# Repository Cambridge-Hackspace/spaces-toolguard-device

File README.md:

# spaces-toolguard-device

The ToolGuard box: its firmware, and the boards it runs on (`hardware/`).

A generic tool box for [Cooperative Systems: Spaces][css], the access-control
platform at the [Cambridge Hackspace][hackspace]. One image, configured at
setup into whichever of these a machine -- or a door, or a room -- needs: a
badge reader that asks the edge and shows the answer on a 16x2 LCD; a reader
that also switches the machine; a reader that watches it work and meters the
time; a plug with no reader at all; a door box that releases a latch for the
pulse the platform names; and, on any of them, a stop button anyone may press.
A door, a tool and a room are the same resource with different bindings (CS:S
#182), and this box speaks the resource-shaped local wire.

> Work in progress. The protocol core and the display model are host-tested, and
> the firmware compiles for all four chips in CI. **Only an ESP32-C6 Super Mini
> has run it**, on the bench: the reader, the panel, a card's round trip to the
> edge, and an over-the-air update with its rollback. Its stop button, relay,
> strike and sense input have not been wired yet. The C5, C3 and S3 pin maps
> compile and nothing more, since none of those boards exists here yet.

## What it is, and is not

The box **asks**, **reports**, and — only if it is configured to switch the
machine — **energizes**, and then only on an explicit yes *and* an unexpired
lease from the edge. The protocol, the session, the lease and the metering are
`spaces_device::Module` from [`spaces-firmware`][sf]; this crate adds the
panel, the card reader, the relay, the sense input, the stop button, and the
setup page that says which of those are wired. The roles are independent and
are settings, not builds: a box registers as whatever it is configured to be,
and the platform binds it to a tool in those roles.

It is **access control and metering, not a safety device.** It must never
replace a door interlock, a guard, or an emergency stop — the stop button
included, which goes through this firmware, a lease and a Wi-Fi link.
[`docs/INSTALLING.md`](docs/INSTALLING.md) opens with why.

## Layout

| Path | What it is |
|---|---|
| `toolguard-core/` | the box as a `spaces_device::Device`: the glue over `spaces_device::Module`, the display model, and how usage is sensed. No hardware, no I/O, host-tested |
| `toolguard-fw/` | the ESP-IDF firmware: RC522 over SPI, 1602 over I2C, three chips |
| `hardware/` | the boards, as atopile and KiCad sources; licensed separately (see below) |

The protocol is not redefined here. `Module`, the topics and the wire types come
from [`spaces-firmware`][sf]'s `spaces-device`, pinned by tag in `Cargo.toml`
(currently `v0.10.0`), so this box and every other module speak the same wire by
construction.

**The local wire is signed.** A box that registration gave a command key seals
every card, stop and usage report with it, and acts on no lease or answer its
edge did not seal for it (CS:S #249; `Online::module`). A box with no key runs
unsigned and logs a warning saying so. **Upgrade the edge first**, to CS:S
v0.6.1 or later: an older edge does not seal, so a signing box ignores every
answer it sends, and every card ends on "no answer".

## The panel is sixteen columns, and that is a design constraint

`toolguard-core/src/screen.rs` decides what a 1602 shows, as a pure function of
state, so "does this outcome fit" is a host test rather than something learned
one reflash at a time.

**A known rough edge, found by exactly that test:** `Training required` is 17
characters — the platform's commonest refusal — so it reaches the panel as
`Training require`. The full reason is in the log. Shortening it in the firmware
would mean matching on reason text, which `FIRMWARE.md` warns against ("branch
on the boolean, display the string"), so the truncation stands until there is a
better answer than a lookup table that silently stops matching.

The diagnostic screen is a first-class view rather than an error case: a reader
whose edge is unreachable is the situation a member is most likely to be
standing in front of, so the panel says **which half** is missing and shows the
device's address, which is where `/log` lives.

## Building

The core is plain Rust and runs anywhere. `--target` is required because
`.cargo/config.toml` makes an ESP target the default:

```sh
cargo test -p toolguard-core --target x86_64-unknown-linux-gnu
```

The firmware needs `cargo install ldproxy` and, for the RISC-V chips, the
nightly pinned in `rust-toolchain.toml`. **`MCU` is not optional** — a target
triple alone is ambiguous (`riscv32imc-esp-espidf` maps to the C3, C2 and H2;
`riscv32imac-esp-espidf` to the C6 *and* the C5, so a C5 build is told apart
from a C6 build by `MCU` alone; esp-idf-sys picks the first it supports,
warning as it goes):

```sh
MCU=esp32c6 cargo build --release --target riscv32imac-esp-espidf
MCU=esp32c5 cargo build --release --target riscv32imac-esp-espidf
MCU=esp32c3 cargo build --release --target riscv32imc-esp-espidf
```

**The board is chosen by `BOARD`**, the way the chip is chosen by `MCU`. Each
board's pin map is `toolguard-fw/boards/<board>.toml`, which the firmware's pin
assignment is generated from; left unset, a chip builds its default board
(`c6-supermini`, `c5-devkitc1`, `c3-supermini`, `s3-devkitc1`). A board for a
different chip than `MCU` is refused:

```sh
BOARD=c5-devkitc1 MCU=esp32c5 cargo build --release --target riscv32imac-esp-espidf
```

Build the C5 into its own `CARGO_TARGET_DIR` if you also build the C6 in the
same checkout: they share a target triple, and ESP-IDF's build directory
remembers which chip it was configured for.

The C5 is there for its radio: it is the only one of the four with 5 GHz Wi-Fi,
which takes a tool box out of the 2.4 GHz band the Zigbee mesh shares (#15).

The **S3 is Xtensa**, which upstream rustc cannot target at all, so it needs
Espressif's compiler fork via espup — pin `0.17.1`, since `0.18.0` is yanked:

```sh
cargo install espup --locked --version 0.17.1
espup install --targets esp32s3 --std
. $HOME/export-esp.sh
MCU=esp32s3 cargo +esp build --release --target xtensa-esp32s3-espidf
```

That combination is measured rather than assumed: CI builds all four, and the
`esp` channel does serve the Xtensa target while `rust-toolchain.toml` keeps the
RISC-V chips on plain nightly, so the C6, C5 and C3 do not pay for a forked
compiler.

## Wiring

**If you are installing one of these on a machine, read
[`docs/INSTALLING.md`](docs/INSTALLING.md) instead of this section.** It covers
the safety, the three things you have to measure on your own machine before
wiring anything, both wiring modes, commissioning in order, and what to do when
it does not work. This section is the summary.

Seven pins always: SPI (SCLK, MOSI, MISO, CS) plus RST for the RC522, and
SDA/SCL for the panel. Five more are used only by the roles that need them —
a **sense** input for a box that watches the machine, a **relay** output for one
that switches it, a **stop** input for a momentary switch to GND that ends
the session when anyone presses it, a **strike** output for a door's latch
driver, and a **powered** input that says the watched machine is on (not on
the C3 or the C5, which have no pin left for it). The assignment is a `cfg`-gated tuple in
`toolguard-fw/src/main.rs`, one arm per chip, the reasoning is in
`toolguard-fw/src/board.rs`, and the table in `docs/INSTALLING.md` is checked
against the tuple by a test.

**What the box is, is configuration and not a build.** One image is flashed and
the same board becomes a badge reader beside a laser, a reader that also
switches it, a reader that watches it work, a plug with no reader at all, or a
door box that releases a latch. The
settings are on the device's own setup page and are read at boot; see
`toolguard-fw/src/settings.rs` for each one, its default, and what going wrong
looks like. Two are worth knowing before wiring anything:

- **"Usage measured by"** must be `none` unless something really is wired to
  the sense input. A device that reports zero working time is believed, and on
  a tool billed by working time that bills nothing. On a laser it is `pulses`,
  with "Machine powered by" set; `docs/INSTALLING.md` §3 has why.
- **"Switches the tool"** must be `yes` only if a relay is wired, because it is
  also what makes this device register in the `power` role — and the platform
  will not lease a tool to a box that claims to switch it and does not.

Two electrical notes worth having before wiring anything:

- **The RC522 is 3.3V only.** Its absolute maximum VCC is 3.6V, so power it from
  3V3 and never from 5V. With a 3.3V MCU this is the easy peripheral.
- **The 1602 is the awkward one.** Its HD44780 bias wants ~5V for readable
  contrast, but a backpack powered at 5V idles SDA/SCL at 5V through its own
  pull-ups, and ESP32 GPIOs are not 5V tolerant. The clean fix is to power the
  backpack from 5V and move its pull-ups to 3V3 — one desolder — rather than
  relying on it working anyway. A "dead" 1602 is also very often just its
  contrast trimpot.

## License

The firmware is [AGPL-3.0-or-later](LICENSE), matching the platform and
`spaces-firmware`. One portion has a second copyright: `poll_card` in
`toolguard-fw/src/rc522.rs` is derived from
[`nfc-522`](https://github.com/Cambridge-Hackspace/nfc-522) and is GPL-3.0;
that file's header says exactly what.

The hardware, everything under [`hardware/`](hardware/), is
[CERN-OHL-S-2.0](hardware/LICENSE), the strongly reciprocal CERN Open Hardware
Licence: a software licence says nothing useful about a board someone
manufactures, and this one does.

[css]: https://github.com/Cambridge-Hackspace/cooperative-systems-spaces
[hackspace]: https://cambridgehackspace.com
[sf]: https://github.com/Cambridge-Hackspace/spaces-firmware

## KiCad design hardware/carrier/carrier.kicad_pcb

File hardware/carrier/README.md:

# The ToolGuard carrier board

One board for every ToolGuard box (#24, #25): a socketed Seeed XIAO ESP32-C5,
the RC522 reader, the 16x2 LCD and everything around them, populated to suit
the box. The schematic is [`carrier.py`](carrier.py) (SKiDL); the layout is
`carrier.kicad_pcb` (KiCad 10). **Nothing here has been built yet.**

**The build guide** -- what to fit for each kind of box, the soldering order,
the mechanical stack, wiring and bring-up -- is [`guide/`](guide/): Quarto,
rendered to PDF (through Typst) and HTML. CI builds it on every change (the
"Carrier board (build guide)" artifact) and attaches the PDF to each `v*`
tag's release. To build it here, with KiCad 10 and Quarto:

```sh
cd guide && python3 figures.py && quarto render    # -> _build/guide.pdf
```

The figures are drawn from the board, so they are built, not committed.

## Building it

Needs [uv](https://docs.astral.sh/uv/) and KiCad 10's symbol and footprint
libraries (`/usr/share/kicad/symbols` and `/usr/share/kicad/footprints`, or set
`KICAD10_SYMBOL_DIR` and `KICAD10_FOOTPRINT_DIR`). Nothing needs a login or a
network service.

```sh
uv run python carrier.py   # writes carrier.net, for KiCad's "Import Netlist"
uv run python check.py     # the checks CI runs
```

`check.py` checks three things, and fails on any of them:

- **the pin map**: every pin role in `toolguard-fw/boards/c5-xiao-carrier.toml`
  reaches the XIAO pad that file names, and only that one, and nothing else on
  the XIAO is wired;
- **pins against pads**: every connected pin of every part exists as a pad on
  its footprint, read from KiCad's own library;
- **ERC**: no errors and no warnings. The exceptions that are intended (two ideal
  diodes driving one rail, unused pins) are declared in `carrier.py`.

Every part has a fixed tag, so rebuilding the netlist never unlinks the layout.

**The layout** is `carrier.kicad_pcb` in this folder, done by hand in KiCad:
*File → Import → Netlist* with `carrier.net`, after every change to
`carrier.py`. KiCad also makes an empty `carrier.kicad_sch` with the project;
it stays empty. The schematic is `carrier.py`, and the netlist is the only way
the design reaches the layout.
SKiDL prints warnings about KiCad 5-9 library paths when it is imported; they are
for tool versions this board does not use.

## What is on it

| Block | Parts | Fitted on |
|---|---|---|
| USB-C power in | USB4125 (power only), 5.1 k on both CC pins, polyfuse, TVS | every box |
| 7-60 V power in | pluggable terminal, reverse-polarity Schottky, fuse, SMBJ40 TVS, LV2862 buck to 5.17 V | boxes inside a machine (d); left off otherwise |
| Combining the two | an LM66100 ideal diode from each | each input that is fitted |
| The XIAO | two 1x7 sockets; its 5V pin fed through one Schottky (B5819W) | every box |
| I²C at 3.3 V | 4.7 k pull-ups, a Qwiic port | every box |
| The LCD | PCA9306 level shifter to a 5 V I²C header for the backpack | (a), (b), (c) |
| The reader | RC522 module socket; 0-ohm links choose I²C (fitted) or SPI | (a), (b), (c) |
| The joystick | PCF8574 at 0x20, JST-PH 8 (COM, UP, DOWN, LEFT, RIGHT, MID, SET, RST) | (c) |
| The stop button | pluggable terminal, normally closed; RC filter and ESD | (b), (c) |
| The sense input | pluggable terminal, LTV-817S opto, 2.2 k for a 5 V signal | (d) |
| Two outputs | G5V-1 relays (dry contacts, 1 A at 24 V DC), AO3400A drivers with gate pull-downs, flyback diodes, an LED each, pluggable COM/NO/NC terminals | (e) |
| The status light | a plain 3 mm through-hole LED on D6, on the front | every box |
| Mounting | 4 M3 enclosure holes; 4 M2.5 for the LCD's standoffs; 4 M3 for the RC522 (nylon standoffs: metal detunes the antenna) | every box |

The letters are the box configurations in #24. Parts marked `DNP` in the
netlist (the 7-60 V input and buck, the SPI links) are left off by default.

## Facts it rests on, and where they come from

- **The XIAO's pads and GPIOs**: Seeed's XIAO ESP32-C5 pinout and schematic
  rev 1.1. Its 5V pin is VBUS behind a load switch, and its power mux drops to
  the battery input below about 4.33 V, so the 5 V path into it allows only one
  ordinary diode drop. That is why the inputs are combined through ideal diodes.
- **The LV2862**: TI's datasheet. 4-60 V in, 65 V transients, 0.765 V
  reference, non-synchronous (so a catch diode rated 25% over the maximum
  input), 22 µH / 10 µF out / 2.2 µF in / 100 nF boot, SHDN to VIN through
  100 k. 57.6 k over 10 k gives 5.17 V.
- **Every symbol, footprint and pin**: KiCad 10.0.8's libraries, read rather
  than remembered. On the G5V-1, NC is pin 1 and NO is pin 10 (the symbol's
  arm rests on pin 1), the coil is 2 and 9, and the common is 5 and 6.
- **The LCD needs the level shifter**: a PCF8574 at 5 V wants about 3.5 V for a
  logic high, which a 3.3 V bus does not give. With the PCA9306, the backpack's
  own pull-ups can stay.

## Layout guidance

- **Keep the RC522's antenna clear**: no copper, pour, tracks or metal standoffs
  under or close to the module's antenna end, on either layer.
- **Keep the buck converter's loop tight** (LV2862, input capacitor, catch diode,
  inductor) in one corner over solid ground, far from the antenna and I²C.
- **Field wiring on one edge**: the terminals, with K1, K2 and their LEDs.
- **Power on a side edge**: USB-C, the ideal diodes and the 7-60 V terminal,
  with the XIAO's own USB-C facing the same edge, and a route for its antenna
  cable to a vent or plastic.
- **SMD parts on the back** for one-sided assembly; the front carries only the
  LCD header, the RC522 socket and the status LED. Ground on the bottom layer,
  except under the antenna.
- **Every hole and part comes from `carrier.py`**: a re-import deletes footprints
  that are not in the netlist, so add mechanical parts there, not by hand.

## The modules' hole patterns, as measured

Measured with calipers on the Hackspace's own modules (2026-11), centres worked
out from edge-to-edge gaps. Place the hole footprints from these.

**LCD 1602 (QAPASS):** board 79.9 x 36.0 mm; four holes of 2.9 mm on a
**75.0 x 30.9 mm** rectangle, about 2.5 mm in from each edge. The standard 1602
pattern. Takes M2.5.

**RFID-RC522 (blue):** board 39.4 x 60.45 mm, viewed from the front with the
header at the top and the antenna in the lower part. Hole centres:

| hole | from the left edge | from the bottom edge |
|---|---|---|
| top-left | 2.7 mm | 44.3 mm |
| top-right | 36.85 mm | 44.3 mm |
| bottom-left | 7.5 mm | 6.9 mm |
| bottom-right | 32.4 mm | 6.9 mm |

That is a 34.15 mm top pair and a 24.95 mm bottom pair, 37.4 mm apart. It
assumes 3.2 mm holes (3.5 mm was measured, but only 3.2 makes the top row's
widths add up) and a level bottom row. To confirm when the module is to hand,
measure square-on from the bottom-left hole to the left edge and to the bottom
edge. The antenna is between and below the bottom pair: keep the carrier's
copper clear of that whole area plus a few millimetres.

## Ordering

```sh
python3 fab.py        # KiCad 10's pcbnew and kicad-cli; no uv environment needed
```

writes `fab/` (git-ignored: it is built from `carrier.kicad_pcb`):

| File | For |
|---|---|
| `carrier-r1-gerbers.zip` | the bare board: Gerbers and drill files, origin at the bottom-left corner |
| `usb/bom.csv`, `usb/cpl.csv` | assembly of every box except (d): what the fab fits, and where |
| `vin/bom.csv`, `vin/cpl.csv` | assembly for box (d), with the 7-60 V input fitted |
| `*/hand-solder.csv` | the through-hole parts you solder yourself |
| `*/not-fitted.csv` | the parts that variant leaves off |

The BOM uses PCBWay's columns. The fab assembles the back only (every
surface-mount part, the USB-C included); the through-hole parts come loose and
are soldered by hand ([the build guide](guide/guide.qmd)). Run DRC before an
order: `kicad-cli pcb drc carrier.kicad_pcb` reports 0 violations and 0
unconnected items.

## Not decided yet

- **Second sources**: every assembled part has an `MPN` except the generic
  resistors and capacitors, which go by value and package. Where the fab
  offers an equivalent it holds in stock, check it against the rating in the
  part's value (`fab.py` lists any part that has neither).
- **The RC522's header**: its position and pin order on the module were
  assumed, not measured (the guide's "Putting it together").

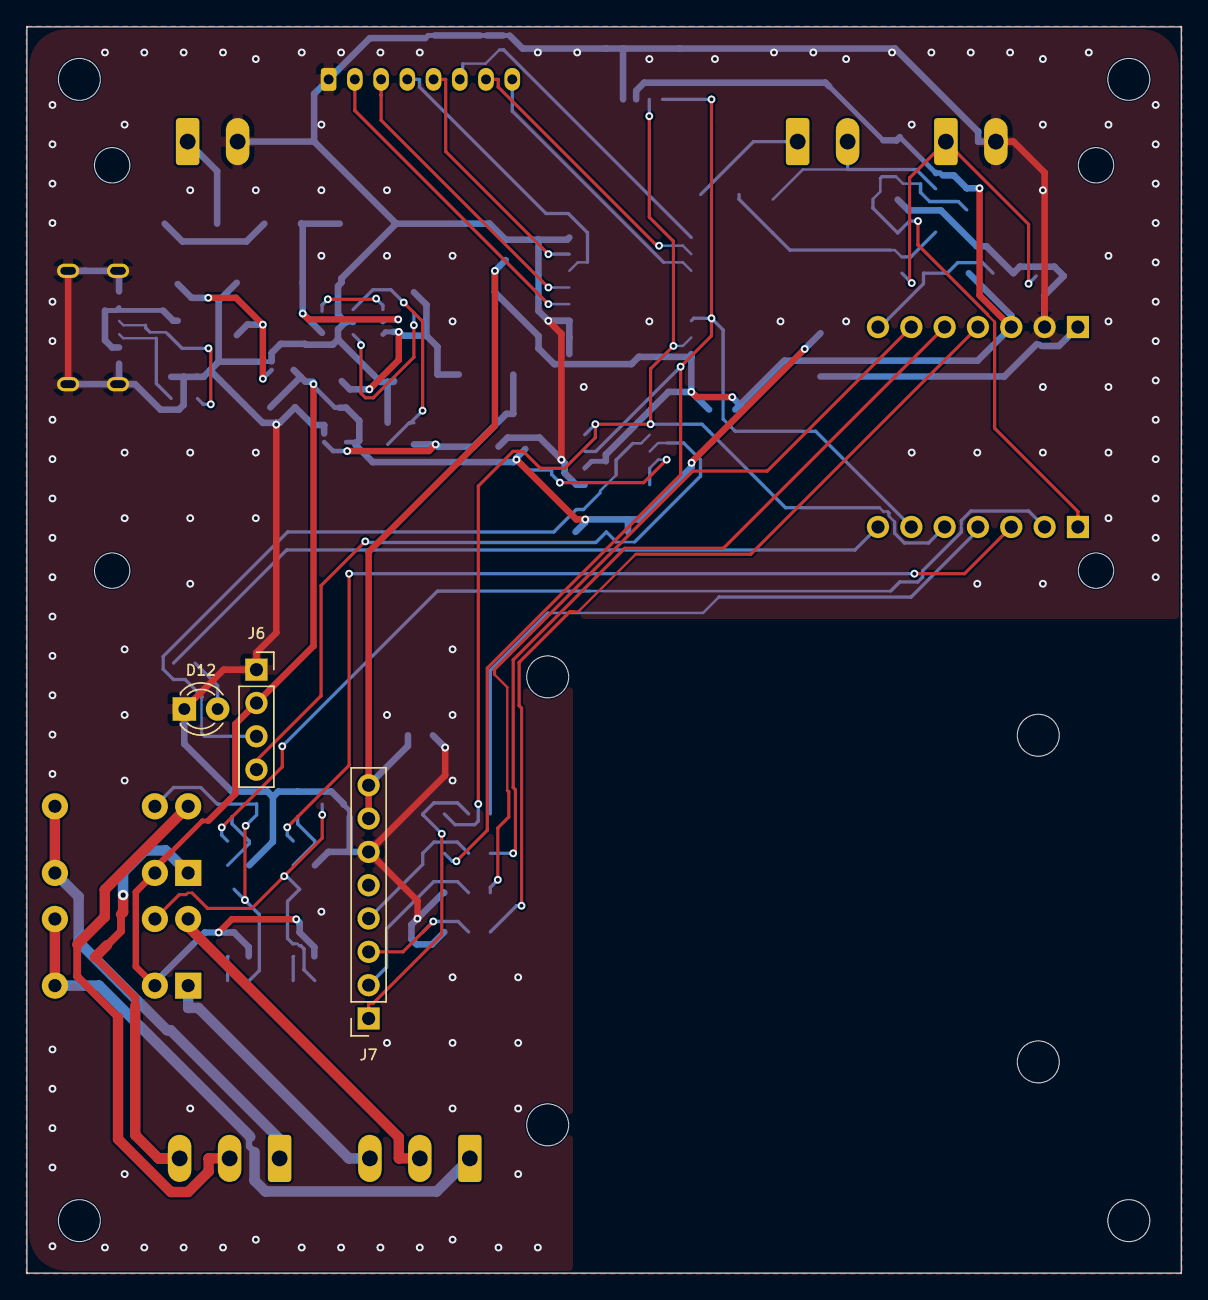
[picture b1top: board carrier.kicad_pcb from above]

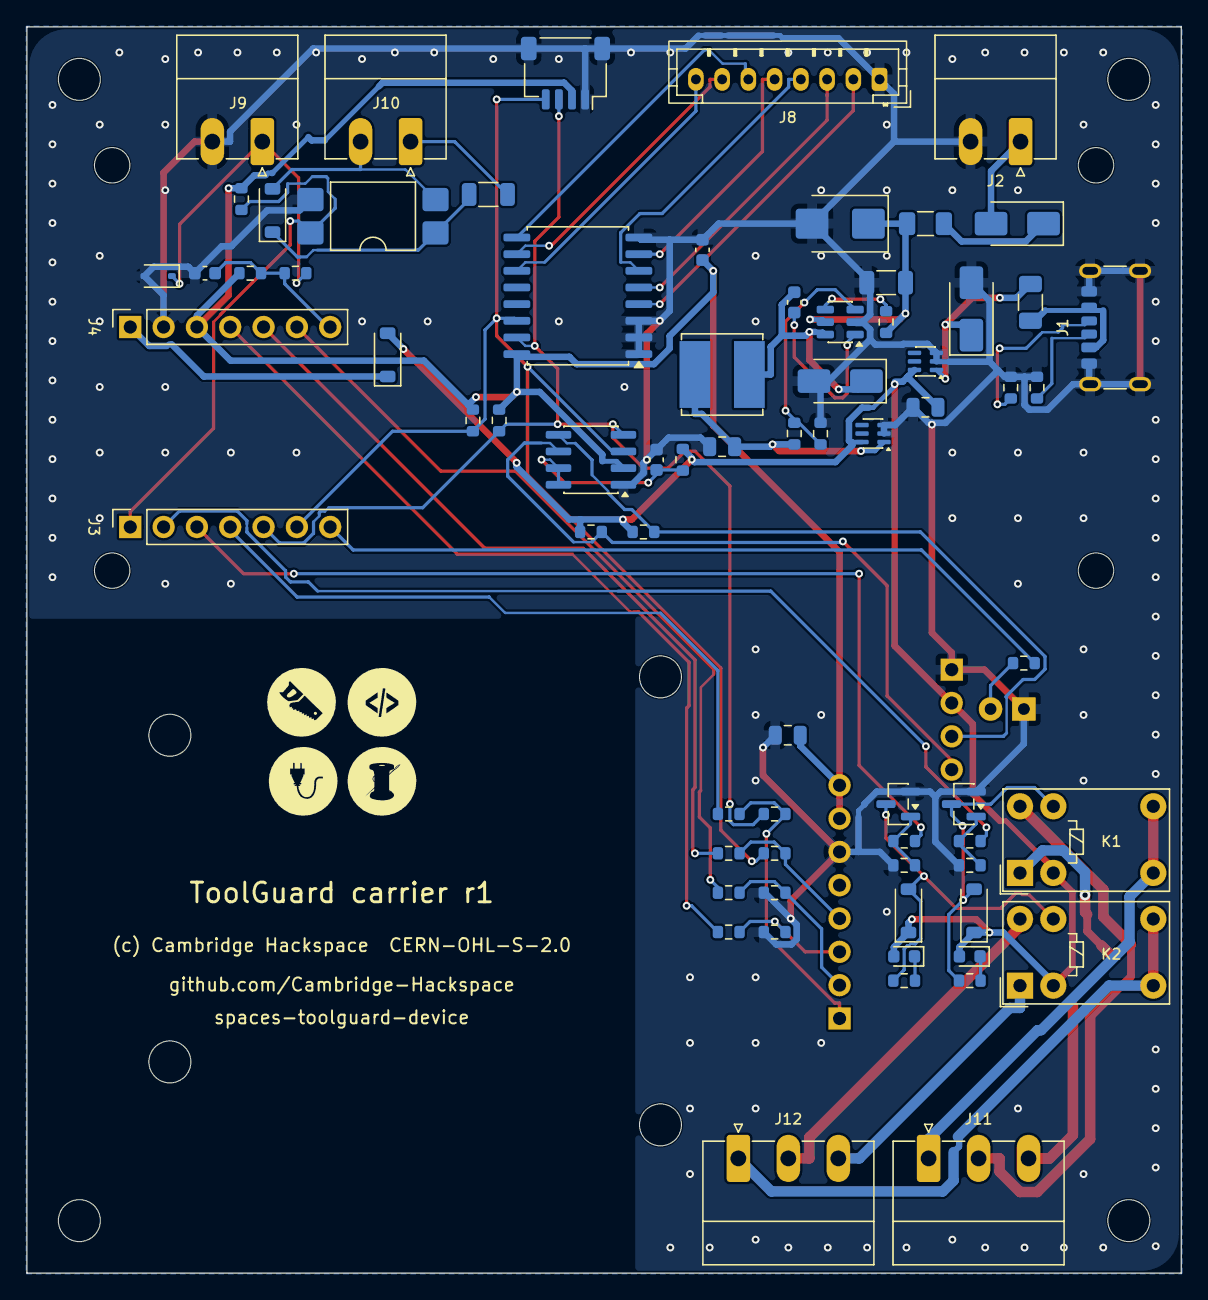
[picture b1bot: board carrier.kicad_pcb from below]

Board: 2 copper layers, 88.0 x 95.0 mm, 86 parts (71 on the bottom side), 58 nets.

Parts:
C1: 2.2uF 100V; C_1206_3216Metric
C2, C5, C7, C8: 100nF; C_0603_1608Metric
C3: 10uF 16V; C_0805_2012Metric
C4, C6: 10uF 10V; C_0805_2012Metric
D1: 5V standoff; D_SMA
D2, D4: 100V 1A; D_SMA
D3: 40V standoff; D_SMB
D5: 40V 1A; D_SOD-123
D6: 3.3V ESD; D_SOD-323
D7, D8, D10: 1N4148W; D_SOD-123
D9, D11: green; LED_0603_1608Metric
D12: red, 3 mm; LED_D3.0mm
F1: 1.1A hold, 6V+; Fuse_1206_3216Metric
F2: 500mA 63V; Fuse_1206_3216Metric
H1, H2, H3, H4, H9, H10, H11, H12: MountingHole; MountingHole_3.2mm_M3
H5, H6, H7, H8: MountingHole; MountingHole_2.7mm_M2.5
J1: USB_C_Receptacle_PowerOnly_6P; USB_C_Receptacle_GCT_USB4125-xx-x_6P_TopMnt_Horizontal
J2, J9, J10: Conn_01x02; PhoenixContact_MC_1,5_2-G-3.81_1x02_P3.81mm_Horizontal
J3, J4: Conn_01x07; PinSocket_1x07_P2.54mm_Vertical
J5: Conn_01x04_MountingPin; JST_SH_SM04B-SRSS-TB_1x04-1MP_P1.00mm_Horizontal
J6: Conn_01x04; PinSocket_1x04_P2.54mm_Vertical
J7: Conn_01x08; PinSocket_1x08_P2.54mm_Vertical
J8: Conn_01x08; JST_PH_B8B-PH-K_1x08_P2.00mm_Vertical
J11, J12: Conn_01x03; PhoenixContact_MC_1,5_3-G-3.81_1x03_P3.81mm_Horizontal
K1, K2: G5V-1; Relay_SPDT_Omron_G5V-1
L1: 22uH, Isat >= 1.6A; L_Bourns_SRN6045TA
Q1, Q2: AO3400A; SOT-23
R1, R2: 5.1k; R_0603_1608Metric
R3, R24, R27: 100k; R_0603_1608Metric
R4: 57.6k 1%; R_0603_1608Metric
R5: 10k 1%; R_0603_1608Metric
R6, R7, R9, R10: 4.7k; R_0603_1608Metric
R8: 200k; R_0603_1608Metric
R11, R12, R13, R14, R15, R16, R17, R18: 0R; R_0603_1608Metric
R19, R29: 1k; R_0603_1608Metric
R20, R22: 10k; R_0603_1608Metric
R21: 2.2k; R_1206_3216Metric
R23, R26: 100R; R_0603_1608Metric
R25, R28: 2.2k; R_0603_1608Metric
U1: LV2862XDDC; SOT-23-6
U2, U3: LM66100DCK; SOT-363_SC-70-6
U4: PCA9306; SOIC-8_3.9x4.9mm_P1.27mm
U5: PCF8574T; SOIC-16W_7.5x10.3mm_P1.27mm
U6: LTV-817S; SMDIP-4_W9.53mm

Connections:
+3V3: C6.1, C7.1, J4.3, J5.2, J7.7, J7.8, R6.2, R7.2, R20.2, R22.2, U4.2, U5.16
+5V: C4.1, D5.2, D8.1, D9.2, D10.1, D11.2, J6.2, K1.2, K2.2, R8.2, R9.2, R10.2, U2.6, U3.6
+5V2_BUCK: C3.1, L1.2, R4.1, U3.1
BUCK_FB: R4.2, R5.1, U1.3
BUCK_SW: C2.2, D4.1, L1.1, U1.6
CS: J3.4, R15.2
GND: C1.2, C3.2, C4.2, C5.2, C6.2, C7.2, C8.2, D1.2, D3.2, D4.2, D6.2, D12.1, J1.A12, J1.B12, J1.SH, J2.2, J4.2, J5.1, J5.MP, J6.1, J7.6, J8.1, J9.2, Q1.2, Q2.2, R1.2, R2.2, R5.2, R13.2, R14.2, R24.2, R27.2, U1.2, U2.2, U2.3, U3.2, U3.3, U4.1, U5.1, U5.2, U5.3, U5.8, U6.3
JOY_DOWN: J8.3, U5.5
JOY_LEFT: J8.4, U5.6
JOY_MID: J8.6, U5.9
JOY_RIGHT: J8.5, U5.7
JOY_RST: J8.8, U5.11
JOY_SET: J8.7, U5.10
JOY_UP: J8.2, U5.4
K1_COIL: D8.2, K1.9, Q1.3, R25.2
K1_COM: J11.1, K1.5, K1.6
K1_GATE: Q1.1, R23.2, R24.1
K1_LED: D9.1, R25.1
K1_NC: J11.3, K1.1
K1_NO: J11.2, K1.10
K2_COIL: D10.2, K2.9, Q2.3, R28.2
K2_COM: J12.1, K2.5, K2.6
K2_GATE: Q2.1, R26.2, R27.1
K2_LED: D11.1, R28.1
K2_NC: J12.3, K2.1
K2_NO: J12.2, K2.10
LIGHT: J3.7, R29.1
LVL_EN: C5.1, R8.1, U4.7, U4.8
MISO: J4.5, R16.2
MOSI: J4.4, R18.2
unnamed: J1.A5, R1.1
unnamed: J1.B5, R2.1
unnamed: R3.2, U1.4
unnamed: C2.1, U1.1
unnamed: D12.2, R29.2
RC_MISO: J7.4, R12.1, R16.1
RC_MOSI: J7.3, R14.1, R18.1
RC_SCK: J7.2, R13.1, R17.1
RC_SDA: J7.1, R11.1, R15.1
RELAY: J3.2, R23.1
SCL: J3.6, J5.4, R7.1, R12.2, U4.3, U5.14
SCLK: J4.6, R17.2
SCL_5V: J6.4, R10.1, U4.6
SDA: J3.5, J5.3, R6.1, R11.2, U4.4, U5.15
SDA_5V: J6.3, R9.1, U4.5
SENSE: J3.1, R22.1, U6.4
SENSE_LED: D7.1, R21.2, U6.1
SENSE_N: D7.2, J10.2, U6.2
SENSE_P: J10.1, R21.1
STOP: C8.1, J4.7, R19.2, R20.1
STOP_IN: D6.1, J9.1, R19.1
STRIKE: J3.3, R26.1
VBUS: F1.1, J1.A9, J1.B9
VBUS_F: D1.1, F1.2, U2.1
VIN: C1.1, D3.1, F2.2, R3.1, U1.5
VIN_RAW: D2.2, J2.1
VIN_RP: D2.1, F2.1
XIAO_5V: D5.1, J4.1

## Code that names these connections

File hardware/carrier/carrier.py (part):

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    vin_rp = Net("VIN_RP")
    d_rev = part("Device", "D_Schottky", "D_REV", value="100V 1A",
                 footprint="Diode_SMD:D_SMA", mpn="SS110", note="reverse polarity", dnp=True)
    vin_raw += pin(d_rev, "A")
    vin_rp += pin(d_rev, "K")
    vin = Net("VIN")
    vin.drive = POWER
    f_vin = part("Device", "Fuse", "F_VIN", value="500mA 63V",
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    d_xiao = part("Device", "D_Schottky", "D_XIAO", value="40V 1A",
                  footprint="Diode_SMD:D_SOD-123", mpn="B5819W")
    v5 += pin(d_xiao, "A")
    xiao_5v += pin(d_xiao, "K")

    nets = {}
    for role, edge in (("SENSE", "D0"), ("RELAY", "D1"), ("STRIKE", "D2"), ("CS", "D3"),
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    # the symbol.
    status = part("Device", "LED", "LED_STATUS", value="red, 3 mm",
                  footprint="LED_THT:LED_D3.0mm", note="front side; lit when D6 is high")
    r("R_STATUS", "1k", nets["LIGHT"], pin(status, "A"))
    gnd += pin(status, "K")

    # --- Mounting --------------------------------------------------------------
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
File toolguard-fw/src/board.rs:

//! Which pin is which, per chip, and the two settings that are not the same
//! on all of them.
//!
//! Everything chip-specific lives here so the rest of the firmware never names
//! a GPIO. `spaces-firmware` hardcodes the C6 in five independent places — the
//! triple, `MCU`, two espflash flags, the partition table's arithmetic — and
//! retargeting it means finding all five; this crate keeps the pins in one
//! module and the chip in `.cargo/config.toml`.
//!
//! ## Why these pins
//!
//! On an ESP32-C6 Super Mini, four pins are effectively unavailable and one of
//! them is a trap:
//!
//! - **GPIO8** carries the board's RGB LED *and* is a strapping pin that
//!   download mode needs pulled HIGH. Espressif: "The strapping combination of
//!   GPIO8 = 0 and GPIO9 = 0 is invalid and will trigger unexpected behavior."
//!   An external peripheral here fights both.
//! - **GPIO9** is BOOT, also strapping, and is the hold-for-setup gesture.
//! - **GPIO12/13** are native USB. The Super Mini has no USB-serial chip, so
//!   these are the only console there is; losing them loses flashing and logs.
//!
//! **GPIO4–7 are usable with care, not unavailable.** GPIO4 and GPIO5 are
//! strapping pins (MTMS, MTDI), sampled at reset and ordinary GPIOs after it;
//! GPIO6 and GPIO7 are JTAG (MTCK, MTDO), unused while the USB-JTAG is the
//! debugger. None of them is flash, which on the C6 is GPIO24–30 and not
//! broken out. The care: nothing may drive 4 or 5 at reset, and GPIO6 has a
//! pull-up after reset, so it is no place for an output that must stay off.
//! GPIO7 already carries the powered input.
//!
//! IO0–IO3, IO14 and IO18–IO23 are the freely usable set: eleven pins, and
//! this firmware uses all eleven when every role is wired (seven always; sense,
//! relay, stop and strike by the roles that need them). GPIO21–23 are pads in
//! the middle of the Super Mini rather than edge pins, so they take a fly lead
//! or a breakout. GPIO4–6 are also the C6's only ADC1 pins that SPI (0–3) does
//! not hold, which matters if the sensed input ever goes analog (#10). The C6's GPIO matrix routes SPI2 and I2C to almost any
//! pin, and ESP-IDF is explicit that below 40 MHz routing through the matrix is
//! no worse than the IOMUX pins — so at 1 MHz this is a pin-budget question and
//! not a capability one.
//!
//! ## On the ESP32-C5 (#15, compile-only)
//!
//! Same family, same triple as the C6, and the reason to want it is the radio:
//! the C5 does 5 GHz Wi-Fi, which takes a tool box out of the 2.4 GHz band the
//! Zigbee mesh shares. Its exclusions, from the IDF v5.5.3 GPIO reference, the
//! DevKitC-1 guide and esptool's boot-mode page:
//!
//! - **GPIO27** is the DevKitC-1's RGB LED and must be high at boot; **GPIO28**
//!   is BOOT (low = download). "GPIO27 = 0 and GPIO28 = 0 is invalid" — the
//!   C6's GPIO8/GPIO9 rule. They take the light and setup roles for that reason.
//! - **GPIO13/14** are USB-Serial-JTAG, the console.
//! - **GPIO15–22** are the module's flash and PSRAM (15 is the PSRAM chip
//!   select on modules that have it).
//! - **GPIO11/12** are UART0, and the DevKitC-1 has a USB-UART bridge on them.
//! - **GPIO2, 7, 25** are strapping.
//!
//! Left: 0, 1, 3, 4, 5, 6, 8, 9, 10, 23, 24 — eleven, which is what the eleven
//! other roles need, so the budget is exactly full on the DevKitC-1 (a board
//! with no UART bridge gets 11 and 12 back). The gain over the C6 is the band
//! and that **sense sits on GPIO1 = ADC1_CH0**, so an analog sense input is
//! possible on this chip where it was not on the C6's map.

//! ## Where the pins actually are
//!
//! Not here, and that is forced rather than chosen: `esp-idf-hal` 0.47 takes
//! pins as CONCRETE types behind plain bounds — `sclk: impl OutputPin + 'd`,
//! `sda: impl InputPin + OutputPin + 'd` — which is also how
//! `spaces-device-espidf` takes them (`impl OutputPin + Send + 'static`). A
//! runtime struct of GPIO numbers would have to be erased to `AnyIOPin` to fit
//! one, losing exactly the compile-time check that stops a pin being used
//! twice — and that check is what caught the S3 using GPIO8 for the LED and
//! for I2C SDA.
//!
//! So each board's assignment is data, `boards/<board>.toml`, and build.rs
//! turns it into a `board_pins!` macro that expands to concrete
//! `pins.gpioN` values in `main.rs`: the compiler still refuses a pin used
//! twice, and build.rs refuses it first with the board and both roles named.
//! The board is chosen by `BOARD`, defaulting per chip. This module holds the
//! reasoning per chip plus the settings that are not pins; the reasoning per
//! pin is in the board files.

/// SPI clock for the RC522, in Hz.
///
/// 1 MHz, well under what the MFRC522 tolerates, chosen for wiring slack: this
/// is a breadboard-and-jumpers peripheral and the data rate is irrelevant when
/// the payload is a card UID.
pub const SPI_HZ: u32 = 1_000_000;

/// The I2C addresses a PCF8574 LCD backpack might answer on.
///
/// The bus is scanned for these at startup rather than one being hardcoded: the
/// PCF8574T answers in `0x20..=0x27` and the PCF8574**A**T in `0x38..=0x3F`,
/// the two parts are visually near-identical, and vendors ship both. A reader
/// that works on one board and shows nothing on the next, for that reason, is a
/// bad afternoon.
pub const LCD_ADDRESSES: &[u8] = &[0x27, 0x3F, 0x20, 0x38];

/// SPI mode for the RC522.
///
/// **Mode 3, and this is not a preference.** ESP-IDF's SPI master on the
/// ESP32-S3 samples MISO on the wrong edge in mode 0, so every register read
/// comes back corrupted while writes still land: the chip resets, polling
/// appears to run, `VersionReg` reads `0x6e` instead of `0x92`, and no tag is
/// ever detected. It presents as "the reader does not work" with nothing in the
/// log (esphome#19065; espressif/esp-idf#7825 and #8815).
///
/// Mode 3 also works on the RISC-V parts, so one value serves all three rather
/// than a per-chip constant nobody can test. The `version()` check at startup
/// is the oracle for this: it reads the exact register the bug corrupts.
///
/// A constant the driver actually passes, not a note: a `bool` saying "use mode
/// 3" would be a second place to disagree with the code.
pub const SPI_MODE: embedded_hal::spi::Mode = embedded_hal::spi::MODE_3;

/// The board this build is for: `BOARD`, or the chip's default (build.rs). Its
/// pin map is `boards/<BOARD>.toml`.
pub const BOARD: &str = env!("TOOLGUARD_BOARD");

/// The chip this build is for, for the boot banner and the device record.
pub const CHIP: &str = if cfg!(esp32c6) {
    "esp32c6"
} else if cfg!(esp32c5) {
    "esp32c5"
} else if cfg!(esp32c3) {
    "esp32c3"
} else if cfg!(esp32s3) {
    "esp32s3"
} else {
    "unknown"
};

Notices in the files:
hardware/carrier/carrier.kicad_pcb:
(c) Cambridge Hackspace  CERN-OHL-S-2.0
